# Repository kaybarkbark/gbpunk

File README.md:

this repository has moved

https://codeberg.org/kaybarkbark/gbpunk

tell microsoft and github to get bent

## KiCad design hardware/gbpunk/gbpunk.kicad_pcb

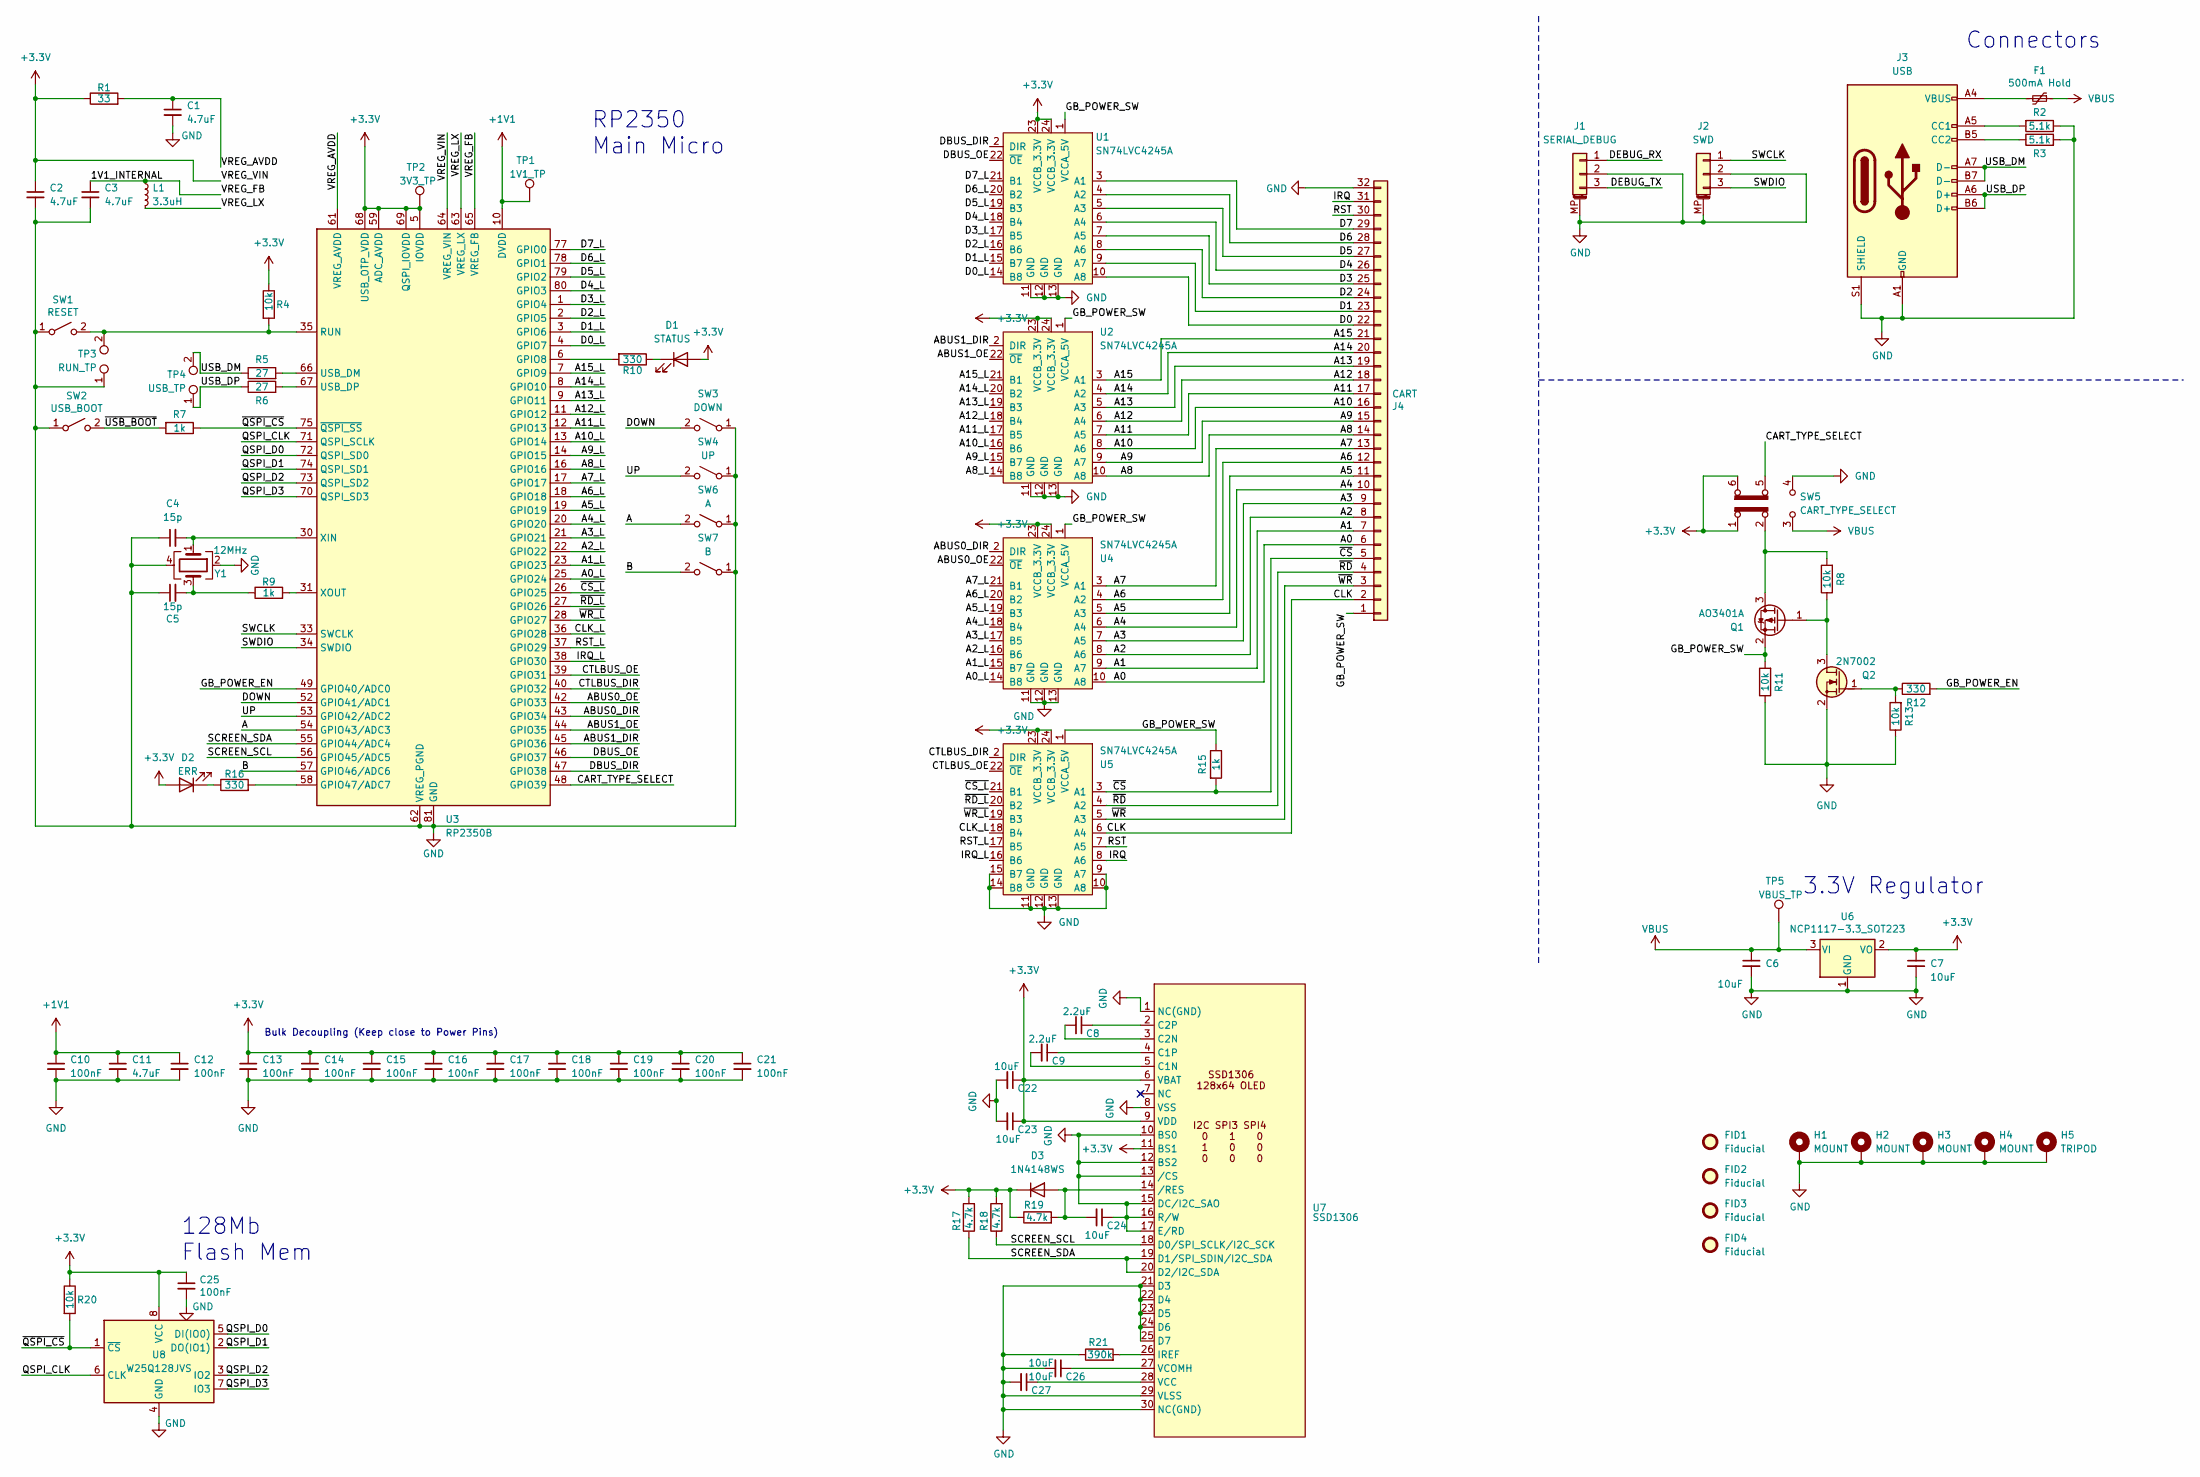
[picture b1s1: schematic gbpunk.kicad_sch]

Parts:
C1, C2, C3, C11: 4.7uF; C_0805_2012Metric
C4, C5: 15p; C_0402_1005Metric
C6, C7: 10uF; C_0603_1608Metric
C8, C9: 2.2uF; C_0603_1608Metric_Pad1.08x0.95mm_HandSolder
C10, C12, C13, C14, C15, C16, C17, C18, C19, C20, C21, C25: 100nF; C_0402_1005Metric
C22, C23, C24, C26, C27: 10uF; C_0603_1608Metric_Pad1.08x0.95mm_HandSolder
D1: STATUS; LED_0603_1608Metric_Pad1.05x0.95mm_HandSolder
D2: ERR; LED_0603_1608Metric_Pad1.05x0.95mm_HandSolder
D3: 1N4148WS; D_SOD-323
F1: 500mA Hold; Fuse_1206_3216Metric_Pad1.42x1.75mm_HandSolder
FID1, FID2, FID3, FID4: Fiducial; Fiducial_1.5mm_Mask3mm
H1, H2, H3, H4: MOUNT; MountingHole_3.2mm_M3_Pad_Via
H5: TRIPOD; MountingHole_8.4mm_M8_Pad_Via
J1: SERIAL_DEBUG; JST_SH_SM03B-SRSS-TB_1x03-1MP_P1.00mm_Horizontal
J2: SWD; JST_SH_SM03B-SRSS-TB_1x03-1MP_P1.00mm_Horizontal
J3: USB; USB_C_Receptacle_G-Switch_GT-USB-7010ASV
J4: CART; PinSocket_1x32_P2.54mm_Vertical
L1: 3.3uH; L_0805_2012Metric
Q1: AO3401A; SOT-23
Q2: 2N7002; SOT-23
R1: 33; R_0603_1608Metric
R2, R3: 5.1k; R_0402_1005Metric
R4, R8, R11, R13, R20: 10k; R_0402_1005Metric
R5, R6: 27; R_0603_1608Metric
R7, R9, R15: 1k; R_0402_1005Metric
R10, R16: 330; R_0603_1608Metric
R12: 330; R_0402_1005Metric
R17, R18, R19: 4.7k; R_0805_2012Metric
R21: 390k; R_0805_2012Metric
SW1: RESET; SW_SPST_EVPBF
SW2: USB_BOOT; SW_SPST_EVPBF
SW3: DOWN; SW_SPST_EVPBF
SW4: UP; SW_SPST_EVPBF
SW5: CART_TYPE_SELECT; SW_DPDT_CK_JS202011JCQN
SW6: A; SW_SPST_EVPBF
SW7: B; SW_SPST_EVPBF
TP1: 1V1_TP; TestPoint_Pad_D1.0mm
TP2: 3V3_TP; TestPoint_Pad_D1.0mm
TP3: RUN_TP; TestPoint_2Pads_Pitch2.54mm_Drill0.8mm
TP4: USB_TP; TestPoint_2Pads_Pitch2.54mm_Drill0.8mm
TP5: VBUS_TP; TestPoint_Pad_D1.0mm
U1, U2, U4, U5: SN74LVC4245A; TSSOP-24_4.4x7.8mm_P0.65mm
U3: RP2350B; QFN-80-1EP_10x10mm_P0.4mm_EP3.4x3.4mm
U6: NCP1117-3.3_SOT223; SOT-223-3_TabPin2
U7: SSD1306
U8: W25Q128JVS; SOIC-8_5.3x5.3mm_P1.27mm
Y1: 12MHz; Crystal_SMD_3225-4Pin_3.2x2.5mm

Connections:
+1V1: C10.1, C11.1, C12.1, TP1.1, U3.10 (DVDD), U3.32 (DVDD), U3.51 (DVDD)
+3.3V: C2.1, C7.1, C13.1, C14.1, C15.1, C16.1, C17.1, C18.1, C19.1, C20.1, C21.1, C22.1, C23.1, C25.1, D1.2 (A), D2.2 (A), D3.1 (K), R1.1, R4.1, R17.2, R18.2, R19.1, R20.1, SW5.1 (A), SW5.6 (C), TP2.1, U1.23 (VCCB_3.3V), U1.24 (VCCB_3.3V), U2.23 (VCCB_3.3V), U2.24 (VCCB_3.3V), U3.5 (IOVDD), U3.15 (IOVDD), U3.24 (IOVDD), U3.29 (IOVDD), U3.41 (IOVDD), U3.50 (IOVDD), U3.59 (ADC_AVDD), U3.60 (IOVDD), U3.64 (VREG_VIN), U3.68 (USB_OTP_VDD), U3.69 (QSPI_IOVDD), U3.76 (IOVDD), U4.23 (VCCB_3.3V), U4.24 (VCCB_3.3V), U5.23 (VCCB_3.3V), U5.24 (VCCB_3.3V), U6.2 (VO), U7.6 (VBAT), U7.9 (VDD), U7.11 (BS1), U8.8 (VCC)
/1V1_INTERNAL: C3.1, L1.1, U3.65 (VREG_FB)
/A: SW6.2 (B), U3.54 (GPIO43/ADC3)
/A0: J4.6, U4.10 (A8)
/A0_L: U3.25 (GPIO24), U4.14 (B8)
/A1: J4.7, U4.9 (A7)
/A1_L: U3.23 (GPIO23), U4.15 (B7)
/A2: J4.8, U4.8 (A6)
/A2_L: U3.22 (GPIO22), U4.16 (B6)
/A3: J4.9, U4.7 (A5)
/A3_L: U3.21 (GPIO21), U4.17 (B5)
/A4: J4.10, U4.6 (A4)
/A4_L: U3.20 (GPIO20), U4.18 (B4)
/A5: J4.11, U4.5 (A3)
/A5_L: U3.19 (GPIO19), U4.19 (B3)
/A6: J4.12, U4.4 (A2)
/A6_L: U3.18 (GPIO18), U4.20 (B2)
/A7: J4.13, U4.3 (A1)
/A7_L: U3.17 (GPIO17), U4.21 (B1)
/A8: J4.14, U2.10 (A8)
/A8_L: U2.14 (B8), U3.16 (GPIO16)
/A9: J4.15, U2.9 (A7)
/A9_L: U2.15 (B7), U3.14 (GPIO15)
/A10: J4.16, U2.8 (A6)
/A10_L: U2.16 (B6), U3.13 (GPIO14)
/A11: J4.17, U2.7 (A5)
/A11_L: U2.17 (B5), U3.12 (GPIO13)
/A12: J4.18, U2.6 (A4)
/A12_L: U2.18 (B4), U3.11 (GPIO12)
/A13: J4.19, U2.5 (A3)
/A13_L: U2.19 (B3), U3.9 (GPIO11)
/A14: J4.20, U2.4 (A2)
/A14_L: U2.20 (B2), U3.8 (GPIO10)
/A15: J4.21, U2.3 (A1)
/A15_L: U2.21 (B1), U3.7 (GPIO9)
/ABUS0_DIR: U3.43 (GPIO34), U4.2 (DIR)
/ABUS0_OE: U3.42 (GPIO33), U4.22 (~OE)
/ABUS1_DIR: U2.2 (DIR), U3.45 (GPIO36)
/ABUS1_OE: U2.22 (~OE), U3.44 (GPIO35)
/B: SW7.2 (B), U3.57 (GPIO46/ADC6)
/CART_TYPE_SELECT: SW5.5 (B), U3.48 (GPIO39)
/CLK: J4.2, U5.6 (A4)
/CLK_L: U3.36 (GPIO28), U5.18 (B4)
/CTLBUS_DIR: U3.40 (GPIO32), U5.2 (DIR)
/CTLBUS_OE: U3.39 (GPIO31), U5.22 (~OE)
/D0: J4.22, U1.10 (A8)
/D0_L: U1.14 (B8), U3.4 (GPIO7)
/D1: J4.23, U1.9 (A7)
/D1_L: U1.15 (B7), U3.3 (GPIO6)
/D2: J4.24, U1.8 (A6)
/D2_L: U1.16 (B6), U3.2 (GPIO5)
/D3: J4.25, U1.7 (A5)
/D3_L: U1.17 (B5), U3.1 (GPIO4)
/D4: J4.26, U1.6 (A4)
/D4_L: U1.18 (B4), U3.80 (GPIO3)
/D5: J4.27, U1.5 (A3)
/D5_L: U1.19 (B3), U3.79 (GPIO2)
/D6: J4.28, U1.4 (A2)
/D6_L: U1.20 (B2), U3.78 (GPIO1)
/D7: J4.29, U1.3 (A1)
/D7_L: U1.21 (B1), U3.77 (GPIO0)
/DBUS_DIR: U1.2 (DIR), U3.47 (GPIO38)
/DBUS_OE: U1.22 (~OE), U3.46 (GPIO37)
/DEBUG_RX: J1.1
/DEBUG_TX: J1.3
/DOWN: SW3.2 (B), U3.52 (GPIO41/ADC1)
/GB_POWER_EN: R12.2, U3.49 (GPIO40/ADC0)
/GB_POWER_SW: J4.1, Q1.2 (S), R11.2, R15.1, U1.1 (VCCA_5V), U2.1 (VCCA_5V), U4.1 (VCCA_5V), U5.1 (VCCA_5V)
/IRQ: J4.31, U5.8 (A6)
/IRQ_L: U3.38 (GPIO30), U5.16 (B6)
/QSPI_CLK: U3.71 (QSPI_SCLK), U8.6 (CLK)
/QSPI_D0: U3.72 (QSPI_SD0), U8.5 (DI(IO0))
/QSPI_D1: U3.74 (QSPI_SD1), U8.2 (DO(IO1))
/QSPI_D2: U3.73 (QSPI_SD2), U8.3 (IO2)
/QSPI_D3: U3.70 (QSPI_SD3), U8.7 (IO3)
/RST: J4.30, U5.7 (A5)
/RST_L: U3.37 (GPIO29), U5.17 (B5)
/SCREEN_SCL: R18.1, U3.56 (GPIO45/ADC5), U7.18 (D0/SPI_SCLK/I2C_SCK)
/SCREEN_SDA: R17.1, U3.55 (GPIO44/ADC4), U7.19 (D1/SPI_SDIN/I2C_SDA), U7.20 (D2/I2C_SDA)
/SWCLK: J2.1, U3.33 (SWCLK)
/SWDIO: J2.3, U3.34 (SWDIO)
/UP: SW4.2 (B), U3.53 (GPIO42/ADC2)
/USB_DM: J3.A7 (D-), J3.B7 (D-), R5.1, TP4.2
/USB_DP: J3.A6 (D+), J3.B6 (D+), R6.1, TP4.1
/VREG_AVDD: C1.1, R1.2, U3.61 (VREG_AVDD)
/VREG_LX: L1.2, U3.63 (VREG_LX)
/~CS_L: U3.26 (GPIO25), U5.21 (B1)
/~CS: J4.5, R15.2, U5.3 (A1)
/~QSPI_CS: R7.1, R20.2, U3.75 (~QSPI_SS), U8.1 (~CS)
/~RD_L: U3.27 (GPIO26), U5.20 (B2)
/~RD: J4.4, U5.4 (A2)
/~USB_BOOT: R7.2, SW2.2 (B)
/~WR_L: U3.28 (GPIO27), U5.19 (B3)
/~WR: J4.3, U5.5 (A3)
GND: C1.2, C2.2, C3.2, C4.1, C5.1, C6.2, C7.2, C10.2, C11.2, C12.2, C13.2, C14.2, C15.2, C16.2, C17.2, C18.2, C19.2, C20.2, C21.2, C22.2, C23.2, C24.1, C25.2, C26.2, C27.2, H1.1, H2.1, H3.1, H4.1, H5.1, J1.2, J1.MP (MountPin), J2.2, J2.MP (MountPin), J3.A1 (GND), J3.A12 (GND), J3.B1 (GND), J3.B12 (GND), J3.S1 (SHIELD), J4.32, Q2.2 (S), R2.1, R3.2, R11.1, R13.1, R21.1, SW1.1 (A), SW2.1 (A), SW3.1 (A), SW4.1 (A), SW5.4 (A), SW6.1 (A), SW7.1 (A), TP3.1, U1.11 (GND), U1.12 (GND), U1.13 (GND), U2.11 (GND), U2.12 (GND), U2.13 (GND), U3.62 (VREG_PGND), U3.81 (GND), U4.11 (GND), U4.12 (GND), U4.13 (GND), U5.9 (A7), U5.10 (A8), U5.11 (GND), U5.12 (GND), U5.13 (GND), U5.14 (B8), U5.15 (B7), U6.1 (GND), U7.1 (NC(GND)), U7.8 (VSS), U7.10 (BS0), U7.12 (BS2), U7.13 (/CS), U7.15 (DC/I2C_SAO), U7.16 (R/W), U7.17 (E/RD), U7.21 (D3), U7.22 (D4), U7.23 (D5), U7.24 (D6), U7.25 (D7), U7.29 (VLSS), U7.30 (NC(GND)), U8.4 (GND), Y1.2, Y1.4
unnamed: C5.2, R9.1, Y1.3
unnamed: D1.1 (K), R10.1
unnamed: D2.1 (K), R16.1
unnamed: C24.2, D3.2 (A), R19.2, U7.14 (/RES)
unnamed: F1.2, J3.A4 (VBUS), J3.A9 (VBUS), J3.B4 (VBUS), J3.B9 (VBUS)
unnamed: J3.A5 (CC1), R2.2
unnamed: J3.B5 (CC2), R3.1
unnamed: Q1.3 (D), R8.2, SW5.2 (B)
unnamed: Q1.1 (G), Q2.3 (D), R8.1
unnamed: Q2.1 (G), R12.1, R13.2
unnamed: R4.2, SW1.2 (B), TP3.2, U3.35 (RUN)
unnamed: R10.2, U3.6 (GPIO8)
unnamed: R16.2, U3.58 (GPIO47/ADC7)
unnamed: R5.2, U3.66 (USB_DM)
unnamed: R6.2, U3.67 (USB_DP)
unnamed: C4.2, U3.30 (XIN), Y1.1
unnamed: R9.2, U3.31 (XOUT)
unnamed: C9.2, U7.5 (C1N)
unnamed: C9.1, U7.4 (C1P)
unnamed: C8.2, U7.3 (C2N)
unnamed: C8.1, U7.2 (C2P)
unnamed: R21.2, U7.26 (IREF)
unnamed: C27.1, U7.28 (VCC)
unnamed: C26.1, U7.27 (VCOMH)
VBUS: C6.1, F1.1, SW5.3 (C), TP5.1, U6.3 (VI)

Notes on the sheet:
Connectors
3.3V Regulator
RP2350 Main Micro
Bulk Decoupling (Keep close to Power Pins)
128Mb Flash Mem

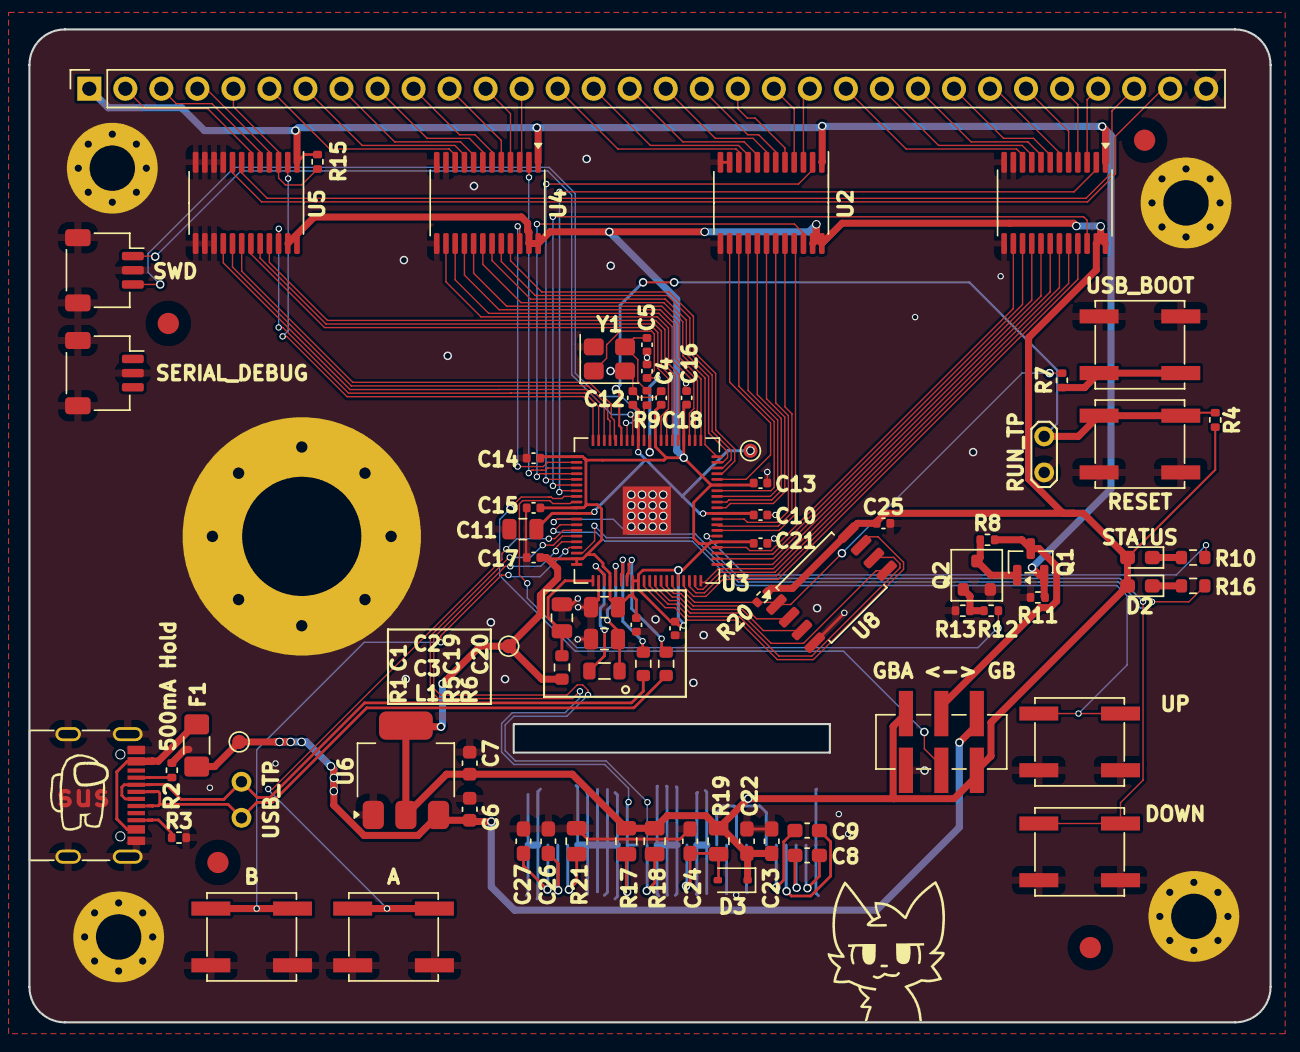
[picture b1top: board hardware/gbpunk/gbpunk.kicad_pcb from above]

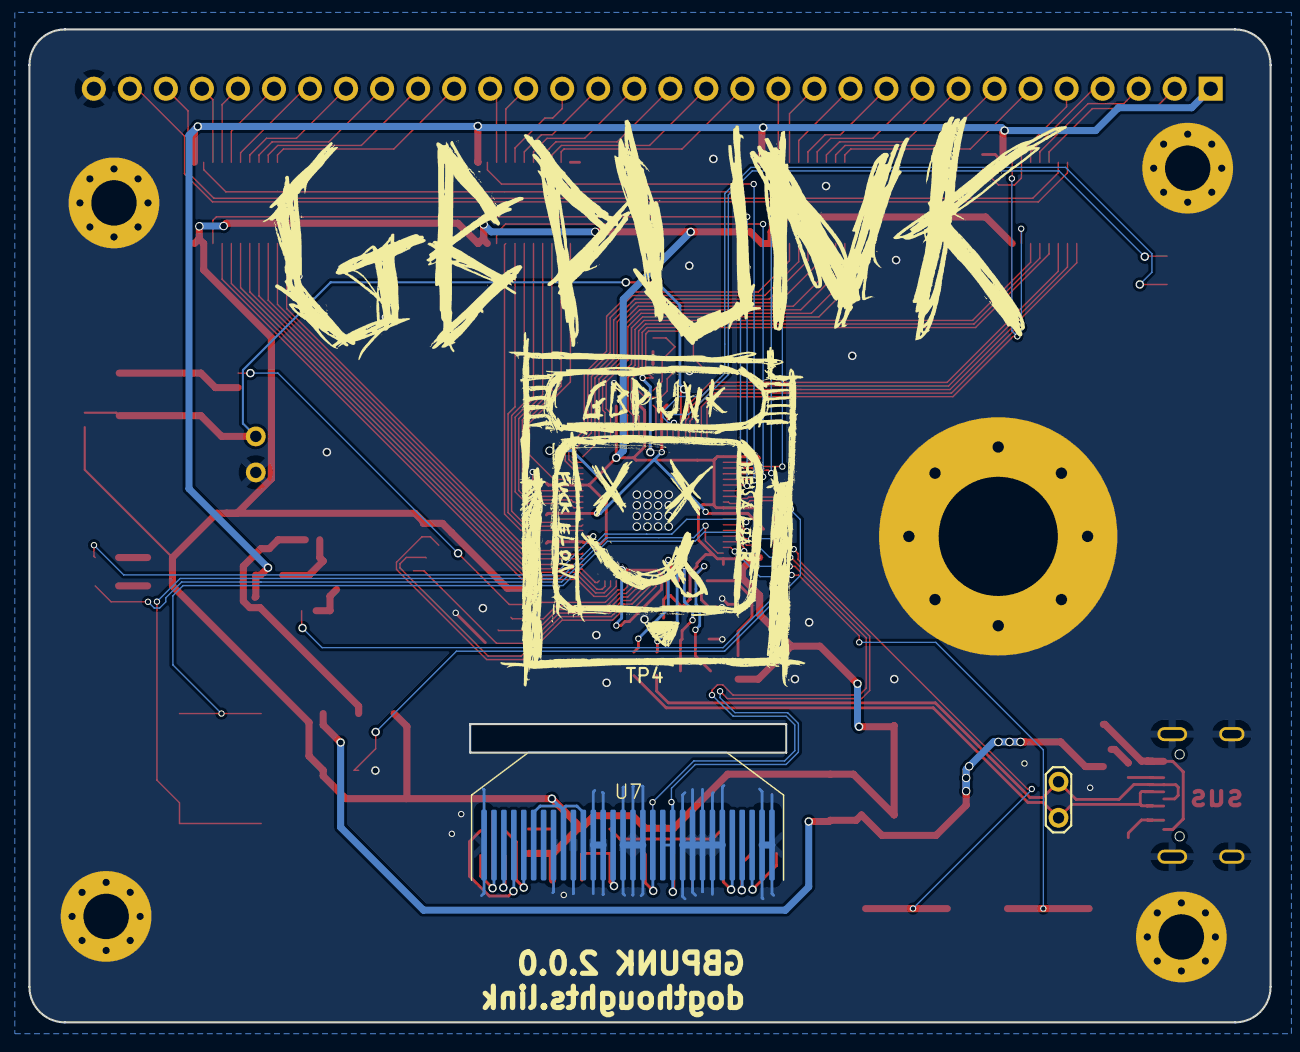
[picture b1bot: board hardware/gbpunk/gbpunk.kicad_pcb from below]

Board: 2 copper layers, 87.5 x 70.0 mm, 88 parts (2 on the bottom side), 119 nets.

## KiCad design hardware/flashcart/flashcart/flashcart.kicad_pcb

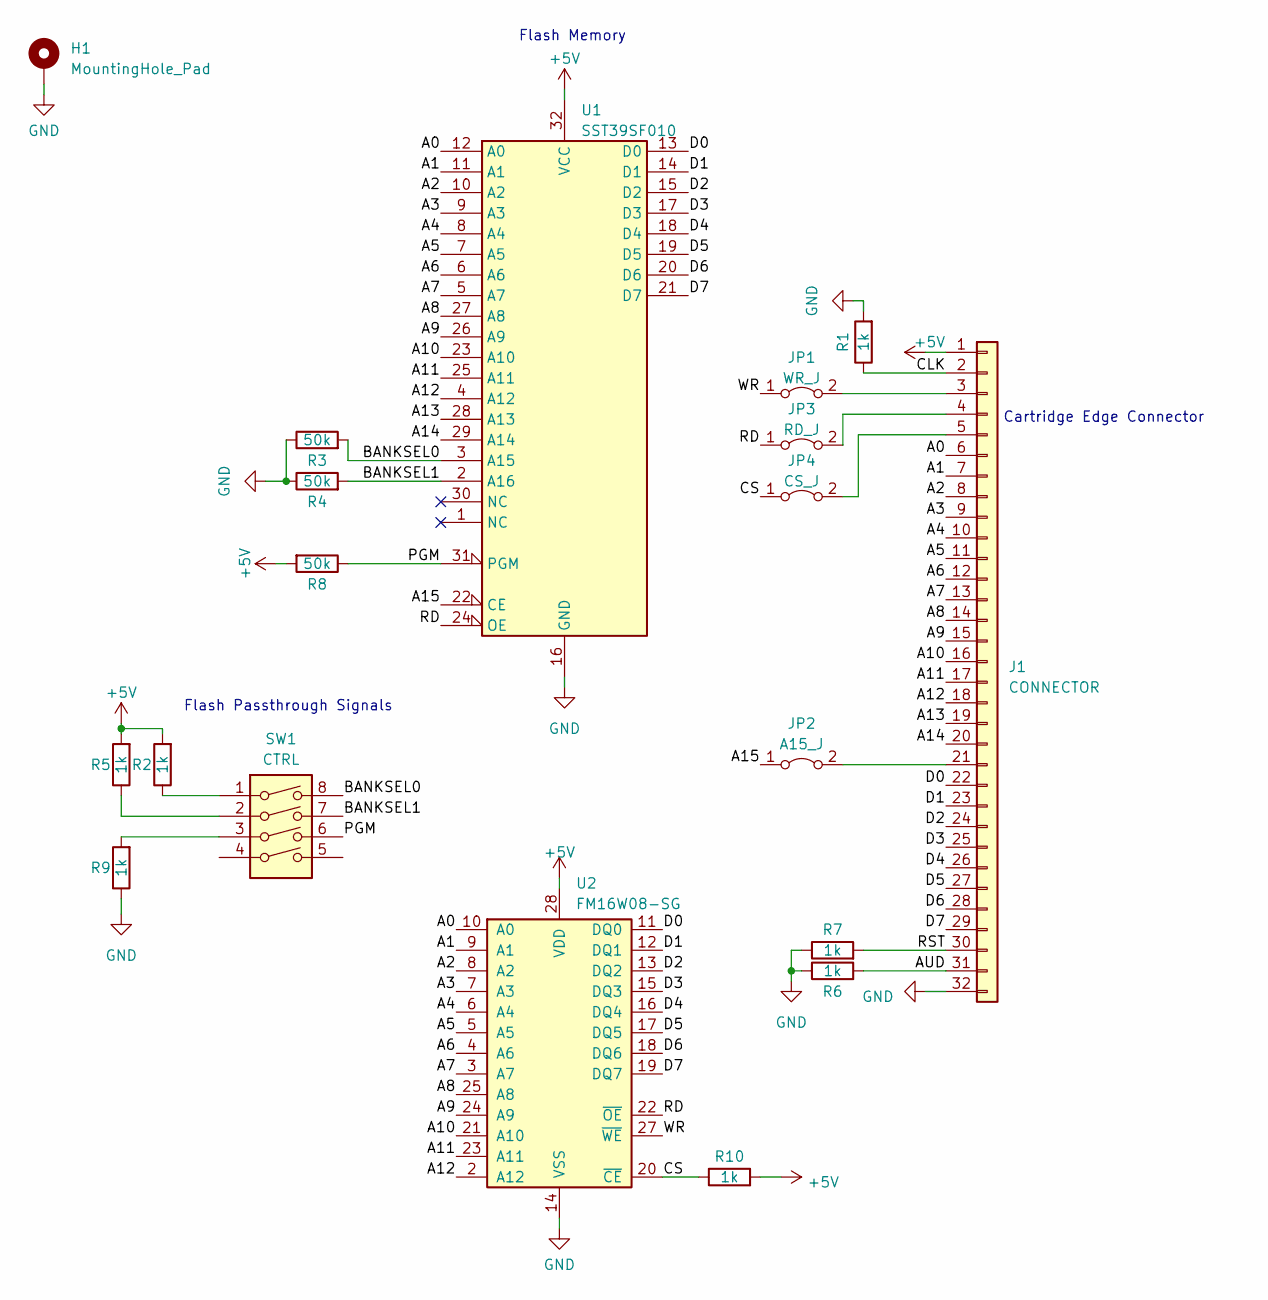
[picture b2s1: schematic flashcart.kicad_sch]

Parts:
H1: MountingHole_Pad; MountingHole_5mm_Pad_Via
J1: CONNECTOR; GameBoy_Cartridge_1x32_P1.50mm_Edge
JP1: WR_J; SolderJumper-2_P1.3mm_Bridged_RoundedPad1.0x1.5mm
JP2: A15_J; SolderJumper-2_P1.3mm_Bridged_RoundedPad1.0x1.5mm
JP3: RD_J; SolderJumper-2_P1.3mm_Bridged_RoundedPad1.0x1.5mm
JP4: CS_J; SolderJumper-2_P1.3mm_Bridged_RoundedPad1.0x1.5mm
R1, R2, R5, R6, R7, R9, R10: 1k; R_0805_2012Metric_Pad1.20x1.40mm_HandSolder
R3, R4, R8: 50k; R_0805_2012Metric_Pad1.20x1.40mm_HandSolder
SW1: CTRL; SW_DIP_SPSTx04_Slide_KingTek_DSHP04TS_W7.62mm_P1.27mm
U1: SST39SF010; TSOP-I-32_14.4x8mm_P0.5mm
U2: FM16W08-SG; SOIC-28W_7.5x17.9mm_P1.27mm

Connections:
+5V: J1.1, R2.2, R5.2, R8.2, R10.2, U1.32 (VCC), U2.28 (VDD)
/A0: J1.6, U1.12 (A0), U2.10 (A0)
/A1: J1.7, U1.11 (A1), U2.9 (A1)
/A2: J1.8, U1.10 (A2), U2.8 (A2)
/A3: J1.9, U1.9 (A3), U2.7 (A3)
/A4: J1.10, U1.8 (A4), U2.6 (A4)
/A5: J1.11, U1.7 (A5), U2.5 (A5)
/A6: J1.12, U1.6 (A6), U2.4 (A6)
/A7: J1.13, U1.5 (A7), U2.3 (A7)
/A8: J1.14, U1.27 (A8), U2.25 (A8)
/A9: J1.15, U1.26 (A9), U2.24 (A9)
/A10: J1.16, U1.23 (A10), U2.21 (A10)
/A11: J1.17, U1.25 (A11), U2.23 (A11)
/A12: J1.18, U1.4 (A12), U2.2 (A12)
/A13: J1.19, U1.28 (A13)
/A14: J1.20, U1.29 (A14)
/A15: JP2.1 (A), U1.22 (CE)
/AUD: J1.31, R6.2
/BANKSEL0: R3.2, SW1.8, U1.3 (A15)
/BANKSEL1: R4.2, SW1.7, U1.2 (A16)
/CLK: J1.2, R1.1
/CS: JP4.1 (A), R10.1, U2.20 (~CE)
/D0: J1.22, U1.13 (D0), U2.11 (DQ0)
/D1: J1.23, U1.14 (D1), U2.12 (DQ1)
/D2: J1.24, U1.15 (D2), U2.13 (DQ2)
/D3: J1.25, U1.17 (D3), U2.15 (DQ3)
/D4: J1.26, U1.18 (D4), U2.16 (DQ4)
/D5: J1.27, U1.19 (D5), U2.17 (DQ5)
/D6: J1.28, U1.20 (D6), U2.18 (DQ6)
/D7: J1.29, U1.21 (D7), U2.19 (DQ7)
/PGM: R8.1, SW1.6, U1.31 (PGM)
/RD: JP3.1 (A), U1.24 (OE), U2.22 (~OE)
/RST: J1.30, R7.2
/WR: JP1.1 (A), U2.27 (~WE)
GND: H1.1, J1.32, R1.2, R3.1, R4.1, R6.1, R7.1, R9.1, U1.16 (GND), U2.14 (VSS)
unnamed: J1.3, JP1.2 (B)
unnamed: J1.4, JP3.2 (B)
unnamed: J1.5, JP4.2 (B)
unnamed: J1.21, JP2.2 (B)
unnamed: R2.1, SW1.1
unnamed: R5.1, SW1.2
unnamed: R9.2, SW1.3

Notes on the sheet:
Cartridge Edge Connector
Flash Memory
Flash Passthrough Signals

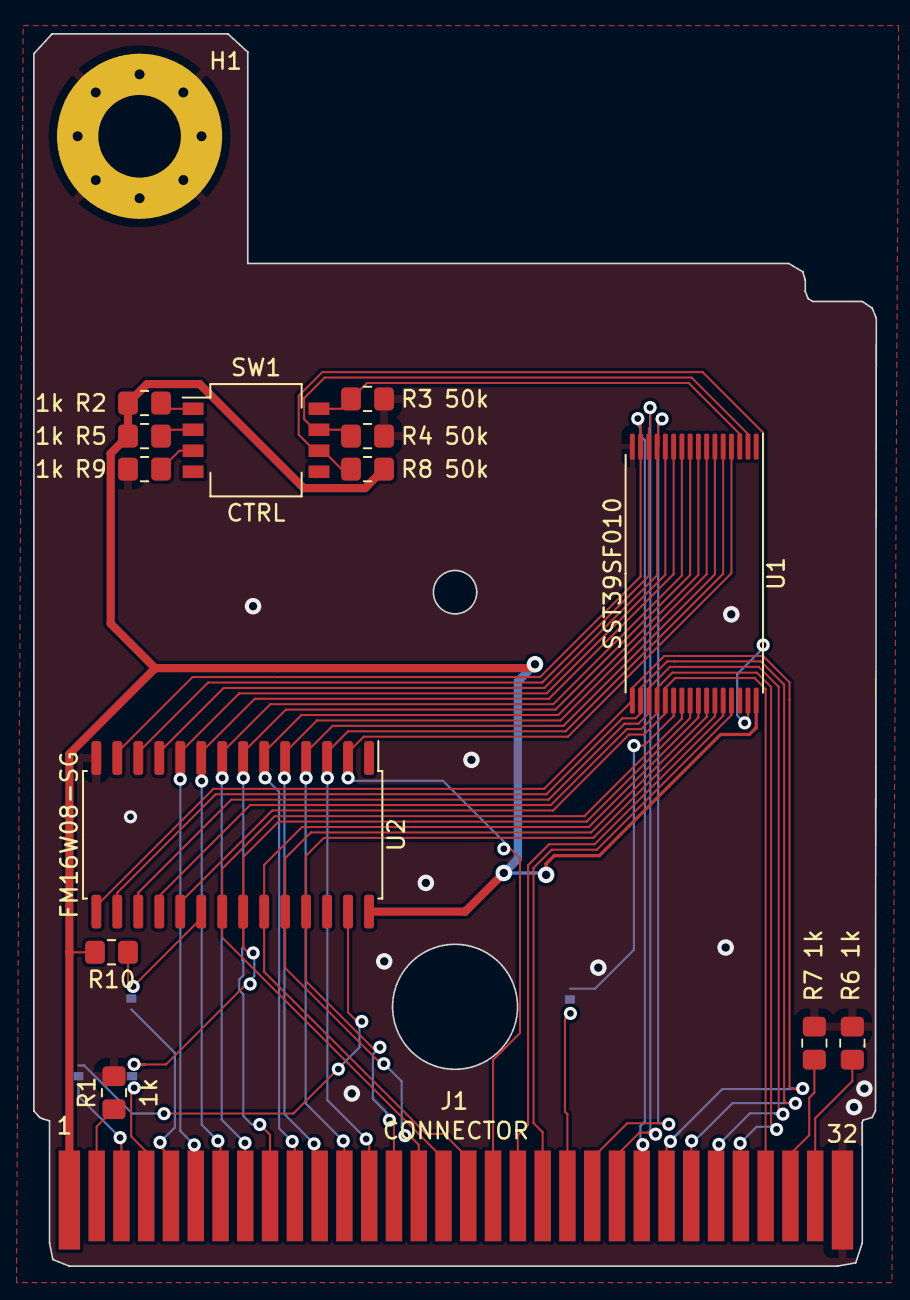
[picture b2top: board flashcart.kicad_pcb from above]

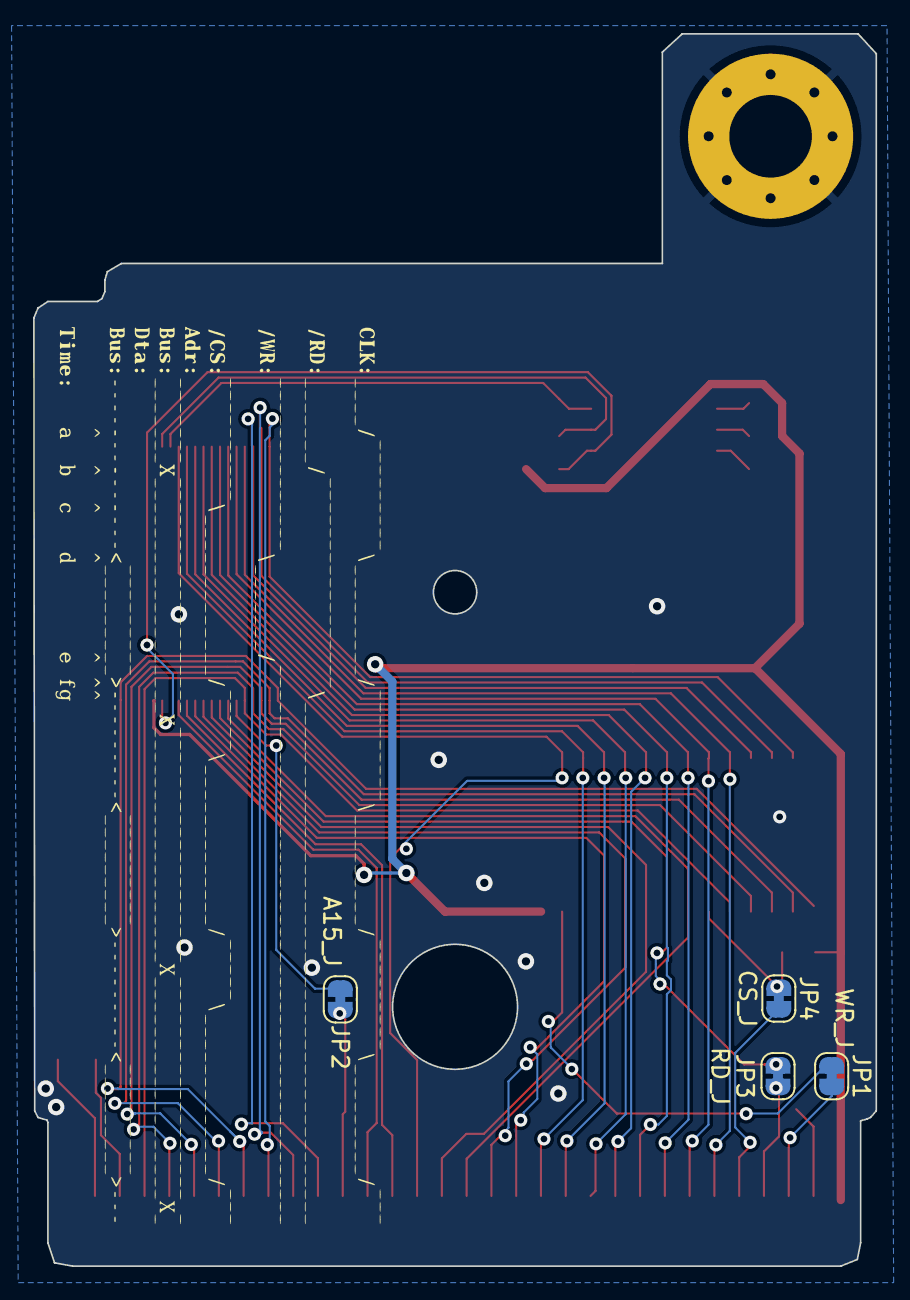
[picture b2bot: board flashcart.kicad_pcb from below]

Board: 2 copper layers, 51.0 x 74.6 mm, 19 parts (4 on the bottom side), 42 nets.

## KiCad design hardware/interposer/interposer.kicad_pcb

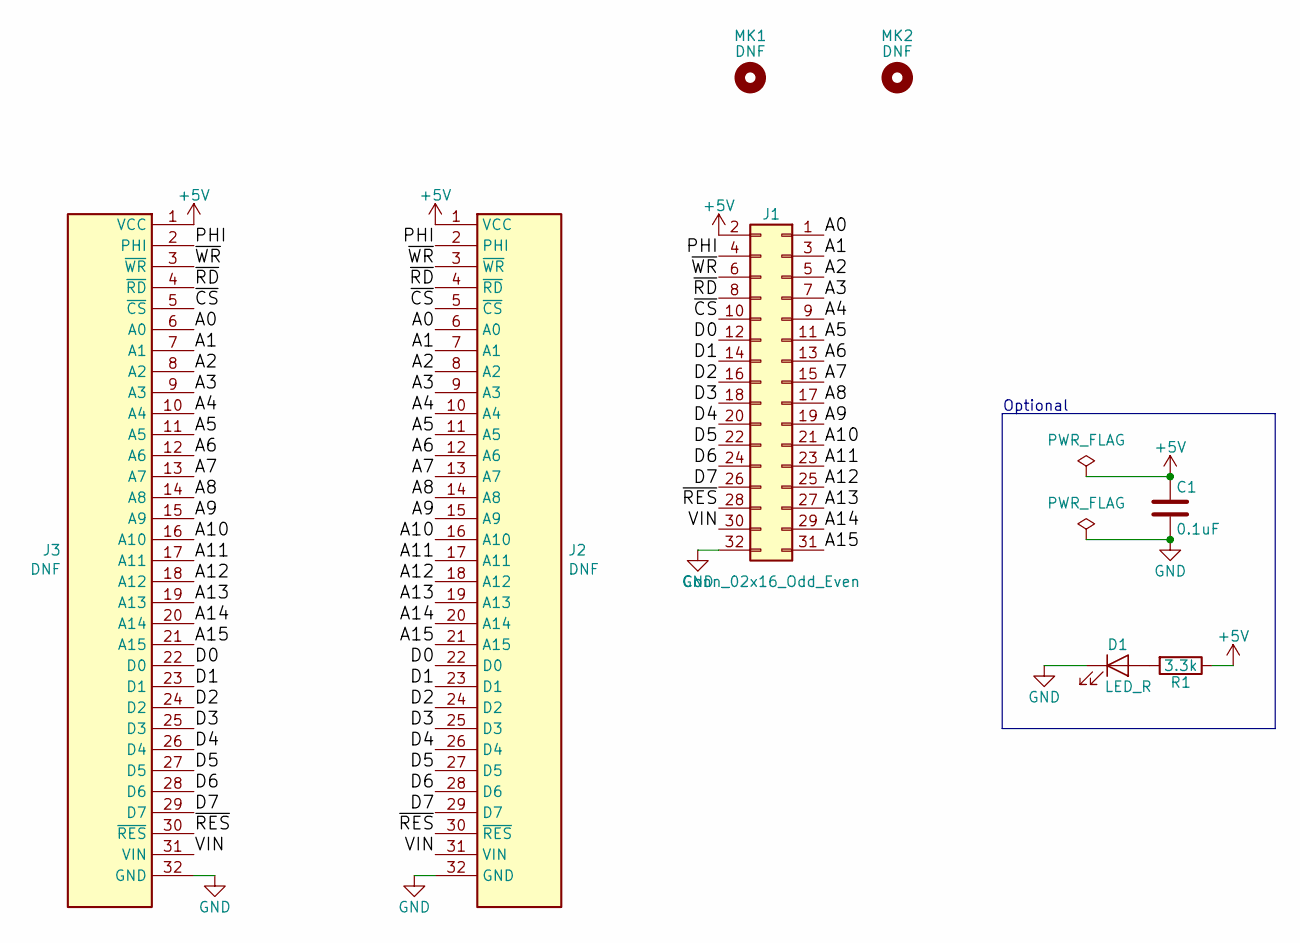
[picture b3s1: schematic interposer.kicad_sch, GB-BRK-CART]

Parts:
C1: 0.1uF; C_0603_1608Metric; Rating 16V X5R; MPN 06035C104KAT4A
D1: LED_R; LED_0603_1608Metric; MPN 150060SS75000
J1: Conn_02x16_Odd_Even; PinHeader_2x16_P2.54mm_Vertical_SMD; MPN 15-91-0800
J2: DNF; GameBoy_Cartridge_1x32_P1.50mm_Edge
J3: DNF; GameBoy_Cartridge_DSLite_1x32_P1.50mm_Socket_Horizontal
MK1: DNF; MountingHole_7.2mm
MK2: DNF; MountingHole_2.3mm
R1: 3.3k; R_0603_1608Metric; Rating 1/10W 5%; MPN CRCW06033K30JNEB

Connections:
+5V: C1.1, J1.2, J2.1 (VCC), J3.1 (VCC), R1.1
/A0: J1.1, J2.6 (A0), J3.6 (A0)
/A1: J1.3, J2.7 (A1), J3.7 (A1)
/A2: J1.5, J2.8 (A2), J3.8 (A2)
/A3: J1.7, J2.9 (A3), J3.9 (A3)
/A4: J1.9, J2.10 (A4), J3.10 (A4)
/A5: J1.11, J2.11 (A5), J3.11 (A5)
/A6: J1.13, J2.12 (A6), J3.12 (A6)
/A7: J1.15, J2.13 (A7), J3.13 (A7)
/A8: J1.17, J2.14 (A8), J3.14 (A8)
/A9: J1.19, J2.15 (A9), J3.15 (A9)
/A10: J1.21, J2.16 (A10), J3.16 (A10)
/A11: J1.23, J2.17 (A11), J3.17 (A11)
/A12: J1.25, J2.18 (A12), J3.18 (A12)
/A13: J1.27, J2.19 (A13), J3.19 (A13)
/A14: J1.29, J2.20 (A14), J3.20 (A14)
/A15: J1.31, J2.21 (A15), J3.21 (A15)
/D0: J1.12, J2.22 (D0), J3.22 (D0)
/D1: J1.14, J2.23 (D1), J3.23 (D1)
/D2: J1.16, J2.24 (D2), J3.24 (D2)
/D3: J1.18, J2.25 (D3), J3.25 (D3)
/D4: J1.20, J2.26 (D4), J3.26 (D4)
/D5: J1.22, J2.27 (D5), J3.27 (D5)
/D6: J1.24, J2.28 (D6), J3.28 (D6)
/D7: J1.26, J2.29 (D7), J3.29 (D7)
/PHI: J1.4, J2.2 (PHI), J3.2 (PHI)
/VIN: J1.30, J2.31 (VIN), J3.31 (VIN)
/~CS: J1.10, J2.5 (~CS), J3.5 (~CS)
/~RD: J1.8, J2.4 (~RD), J3.4 (~RD)
/~RES: J1.28, J2.30 (~RES), J3.30 (~RES)
/~WR: J1.6, J2.3 (~WR), J3.3 (~WR)
GND: C1.2, D1.1 (K), J1.32, J2.32 (GND), J3.32 (GND)
unnamed: D1.2 (A), R1.2

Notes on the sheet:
Optional

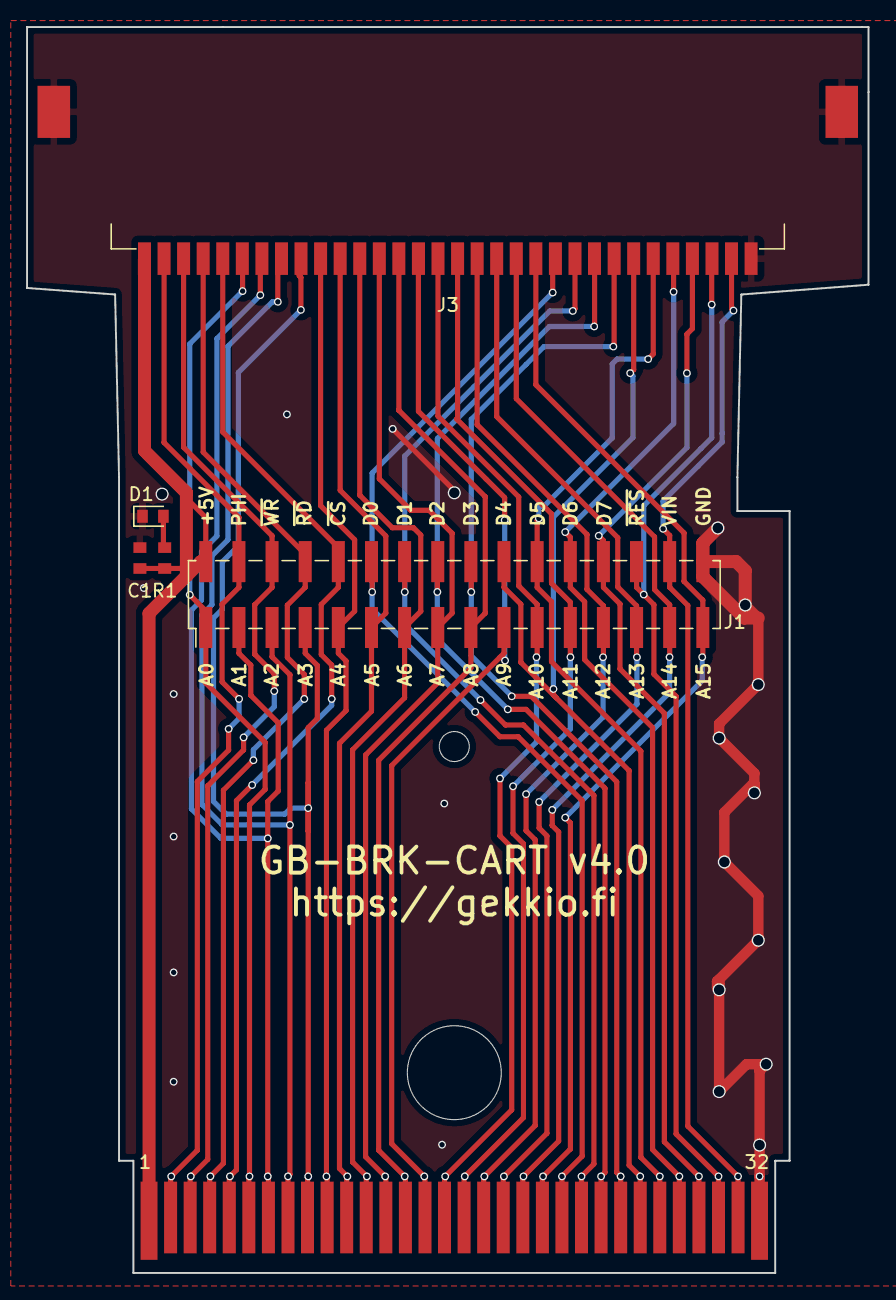
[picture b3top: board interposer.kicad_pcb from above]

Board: 2 copper layers, 64.5 x 95.5 mm, 8 parts (0 on the bottom side), 33 nets.
